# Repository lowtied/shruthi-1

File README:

Shruthi-1, a digital/analog hybrid MIDI monosynth.

This project is a redesign of the original Shruti-1, with a spec'ed up CPU,
and a focus on easy upgrades/modification of the analog section.
The ATMega644p allows new features in the firmware -- a larger selection of
oscillator algorithms, a bigger selection of wavetables, and a tiny sequencer.

Original developer: Emilie Gillet (emilie.o.gillet@gmail.com)

The firmware is released under a GPL3.0 license. It includes a
reimplementation of the formant synthesis algorithm used in Peter Knight's
Cantarino speech synthesizer.

The PCB layouts and schematics (in /hardware/shruthi/design/pcb)
are released under a Creative Commons cc-by-sa 3.0 license - except for some
discontinued filter boards which were released under a cc-by-nc-sa 3.0 license.

Documentation, analyses, simulations and 3D models are released under a
Creative Commons cc-by-sa 3.0 license.

PCB art:
- "saraswati" by Francois Barbut.
- "peacock_face" by Emilie Gillet.
- "radha" by Emilie Gillet.

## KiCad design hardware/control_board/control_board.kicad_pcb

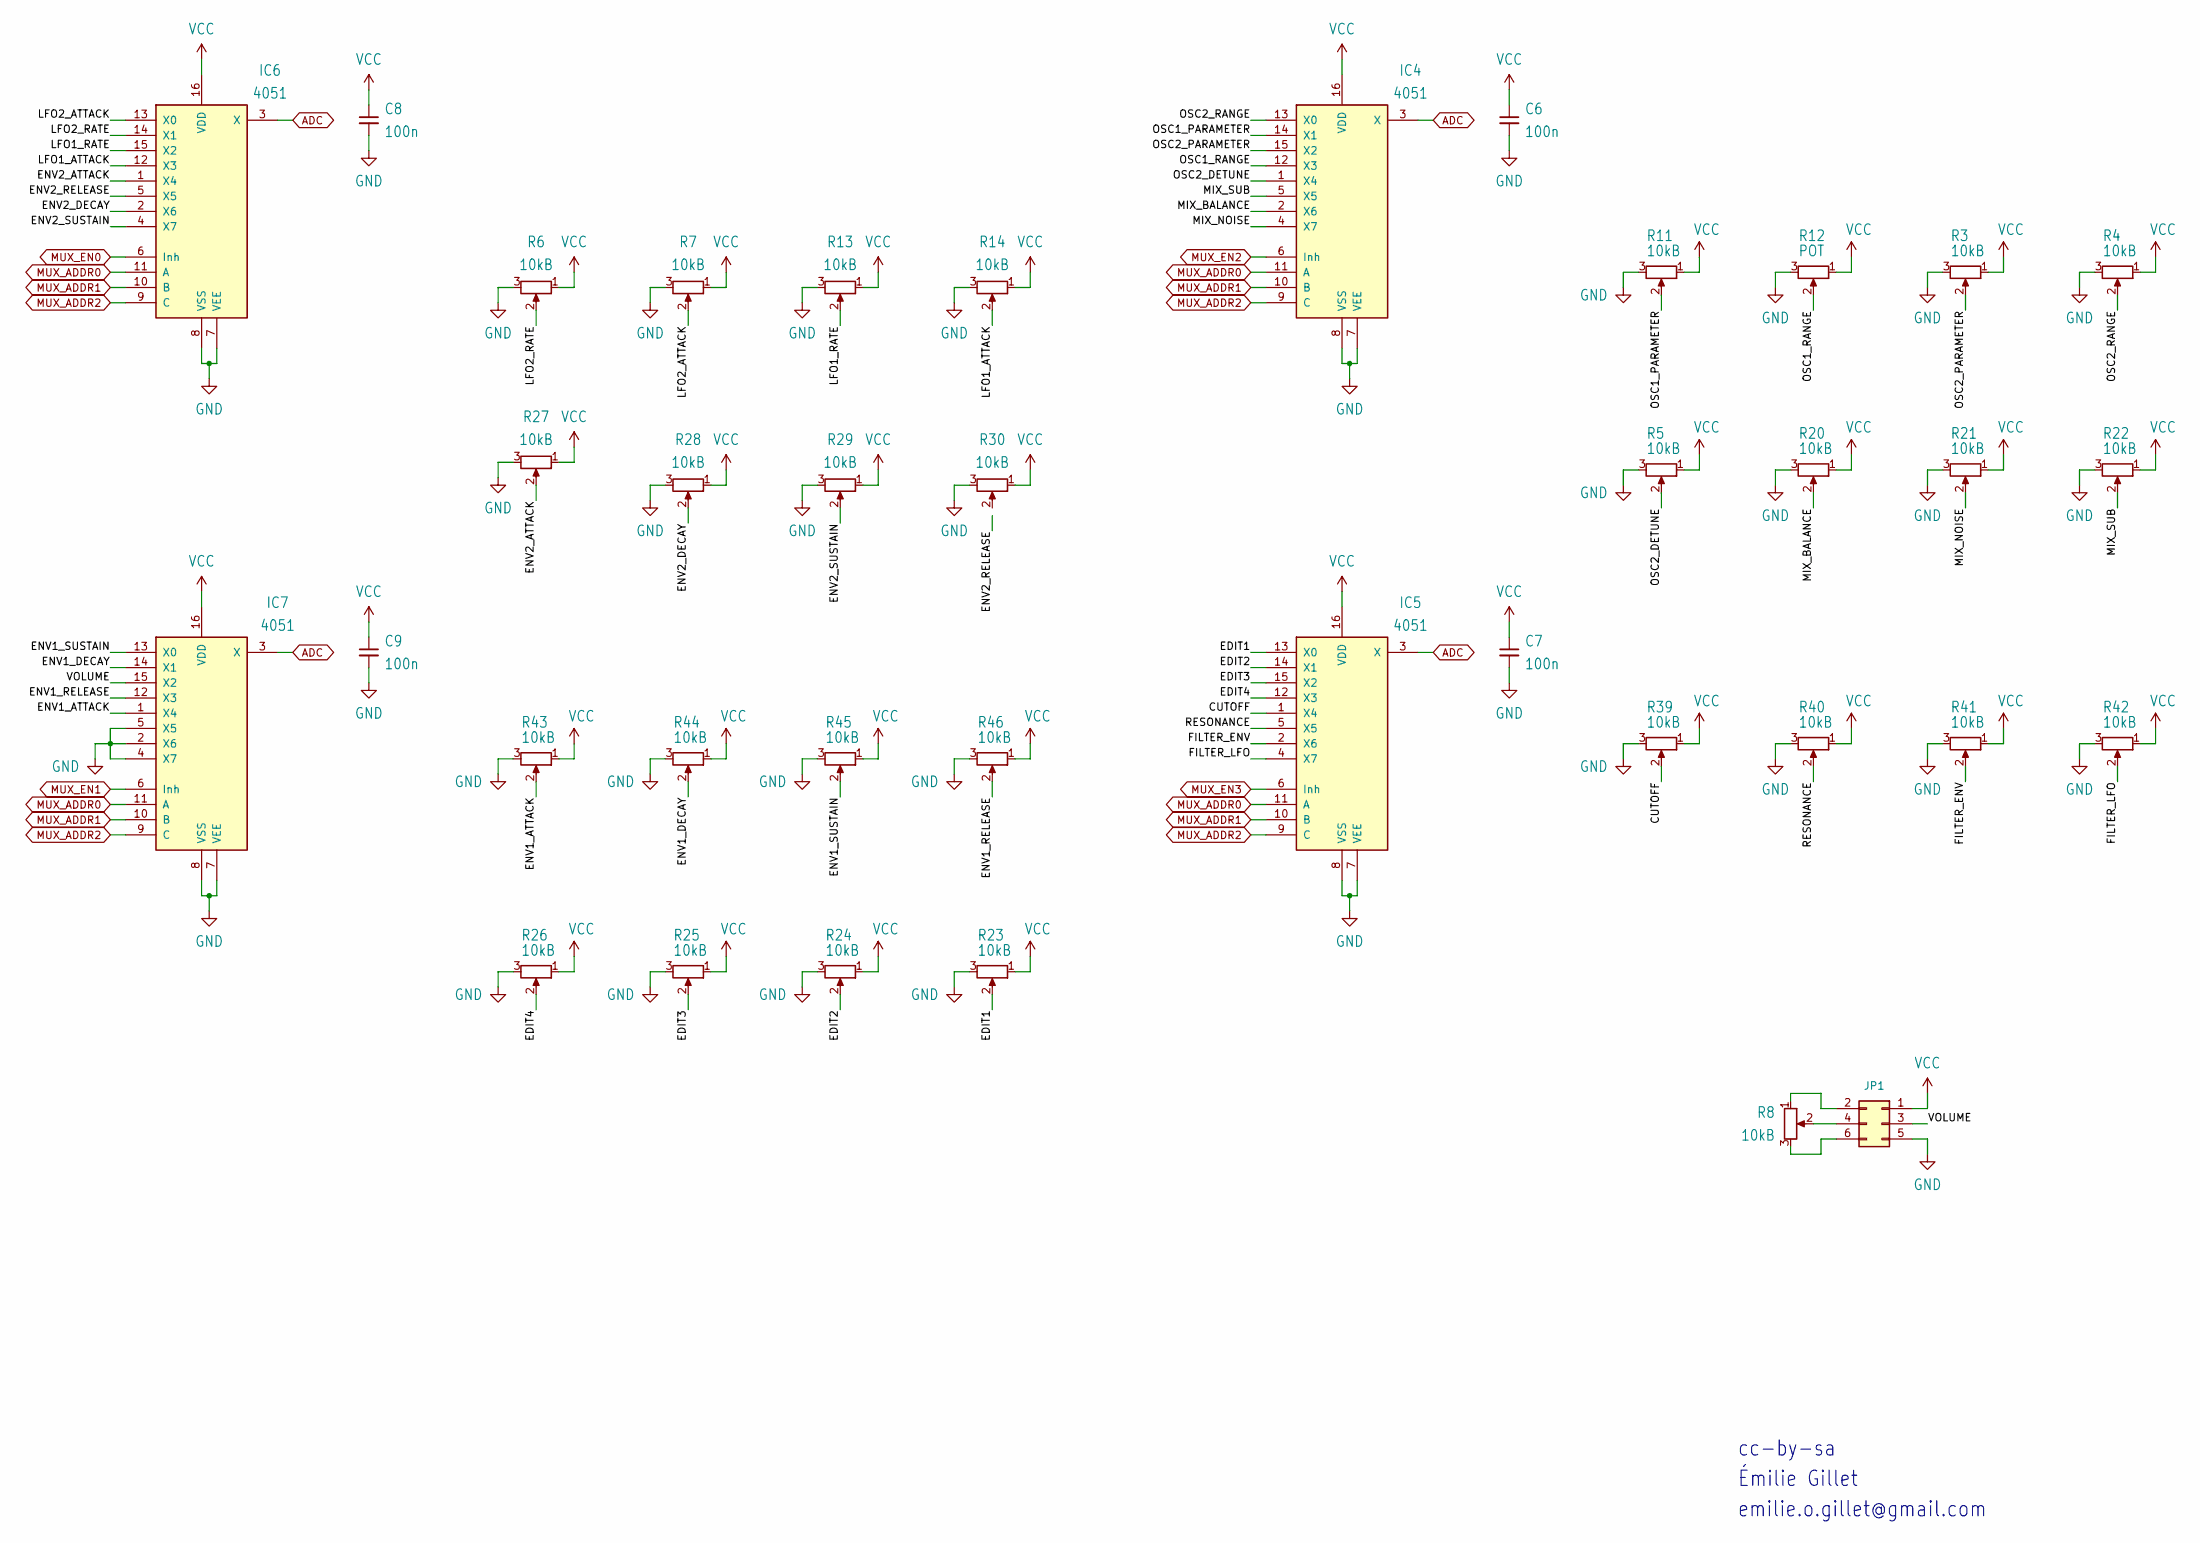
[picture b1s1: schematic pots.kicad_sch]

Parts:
C6, C7, C8, C9: 100n; C025-024X044
IC4, IC5, IC6, IC7: 4051; DIP-16_W7.62mm_Socket_LongPads
JP1: Conn_02x03_Odd_Even; PinHeader_2x03_P2.54mm_Vertical
R3, R4, R5, R6, R7, R8, R11, R13, R14, R20, R21, R22, R23, R24, R25, R26, R27, R28, R29, R30, R39, R40, R41, R42, R43, R44, R45, R46: 10kB; ALPS_POT_VERTICAL
R12: POT; ALPS_POT_VERTICAL

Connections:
/pots/CUTOFF: IC5.1 (X4), R39.2
/pots/EDIT1: IC5.13 (X0), R23.2
/pots/EDIT2: IC5.14 (X1), R24.2
/pots/EDIT3: IC5.15 (X2), R25.2
/pots/EDIT4: IC5.12 (X3), R26.2
/pots/ENV1_ATTACK: IC7.1 (X4), R43.2
/pots/ENV1_DECAY: IC7.14 (X1), R44.2
/pots/ENV1_RELEASE: IC7.12 (X3), R46.2
/pots/ENV1_SUSTAIN: IC7.13 (X0), R45.2
/pots/ENV2_ATTACK: IC6.1 (X4), R27.2
/pots/ENV2_DECAY: IC6.2 (X6), R28.2
/pots/ENV2_RELEASE: IC6.5 (X5)
/pots/ENV2_SUSTAIN: IC6.4 (X7), R29.2
/pots/FILTER_ENV: IC5.2 (X6), R41.2
/pots/FILTER_LFO: IC5.4 (X7), R42.2
/pots/LFO1_ATTACK: IC6.12 (X3), R14.2
/pots/LFO1_RATE: IC6.15 (X2), R13.2
/pots/LFO2_ATTACK: IC6.13 (X0), R7.2
/pots/LFO2_RATE: IC6.14 (X1), R6.2
/pots/MIX_BALANCE: IC4.2 (X6), R20.2
/pots/MIX_NOISE: IC4.4 (X7), R21.2
/pots/MIX_SUB: IC4.5 (X5), R22.2
/pots/OSC1_PARAMETER: IC4.14 (X1), R11.2
/pots/OSC1_RANGE: IC4.12 (X3), R12.2
/pots/OSC2_DETUNE: IC4.1 (X4), R5.2
/pots/OSC2_PARAMETER: IC4.15 (X2), R3.2
/pots/OSC2_RANGE: IC4.13 (X0), R4.2
/pots/RESONANCE: IC5.5 (X5), R40.2
/pots/VOLUME: IC7.15 (X2), JP1.3
ADC: IC4.3 (X), IC5.3 (X), IC6.3 (X), IC7.3 (X); also elsewhere on the board
GND: C6.2, C7.2, C8.2, C9.2, IC4.7 (VEE), IC4.8 (VSS), IC5.7 (VEE), IC5.8 (VSS), IC6.7 (VEE), IC6.8 (VSS), IC7.2 (X6), IC7.4 (X7), IC7.5 (X5), IC7.7 (VEE), IC7.8 (VSS), JP1.5, R3.3, R4.3, R5.3, R6.3, R7.3, R11.3, R12.3, R13.3, R14.3, R20.3, R21.3, R22.3, R23.3, R24.3, R25.3, R26.3, R27.3, R28.3, R29.3, R30.3, R39.3, R40.3, R41.3, R42.3, R43.3, R44.3, R45.3, R46.3; also elsewhere on the board
MUX_ADDR0: IC4.11 (A), IC5.11 (A), IC6.11 (A), IC7.11 (A); also elsewhere on the board
MUX_ADDR1: IC4.10 (B), IC5.10 (B), IC6.10 (B), IC7.10 (B); also elsewhere on the board
MUX_ADDR2: IC4.9 (C), IC5.9 (C), IC6.9 (C), IC7.9 (C); also elsewhere on the board
MUX_EN0: IC6.6 (Inh); also elsewhere on the board
MUX_EN1: IC7.6 (Inh); also elsewhere on the board
MUX_EN2: IC4.6 (Inh); also elsewhere on the board
MUX_EN3: IC5.6 (Inh); also elsewhere on the board
unnamed: JP1.2, R8.1
unnamed: JP1.4, R8.2
unnamed: JP1.6, R8.3
VCC: C6.1, C7.1, C8.1, C9.1, IC4.16 (VDD), IC5.16 (VDD), IC6.16 (VDD), IC7.16 (VDD), JP1.1, R3.1, R4.1, R5.1, R6.1, R7.1, R11.1, R12.1, R13.1, R14.1, R20.1, R21.1, R22.1, R23.1, R24.1, R25.1, R26.1, R27.1, R28.1, R29.1, R30.1, R39.1, R40.1, R41.1, R42.1, R43.1, R44.1, R45.1, R46.1; also elsewhere on the board

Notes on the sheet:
emilie.o.gillet@gmail.com
cc-by-sa
Émilie Gillet

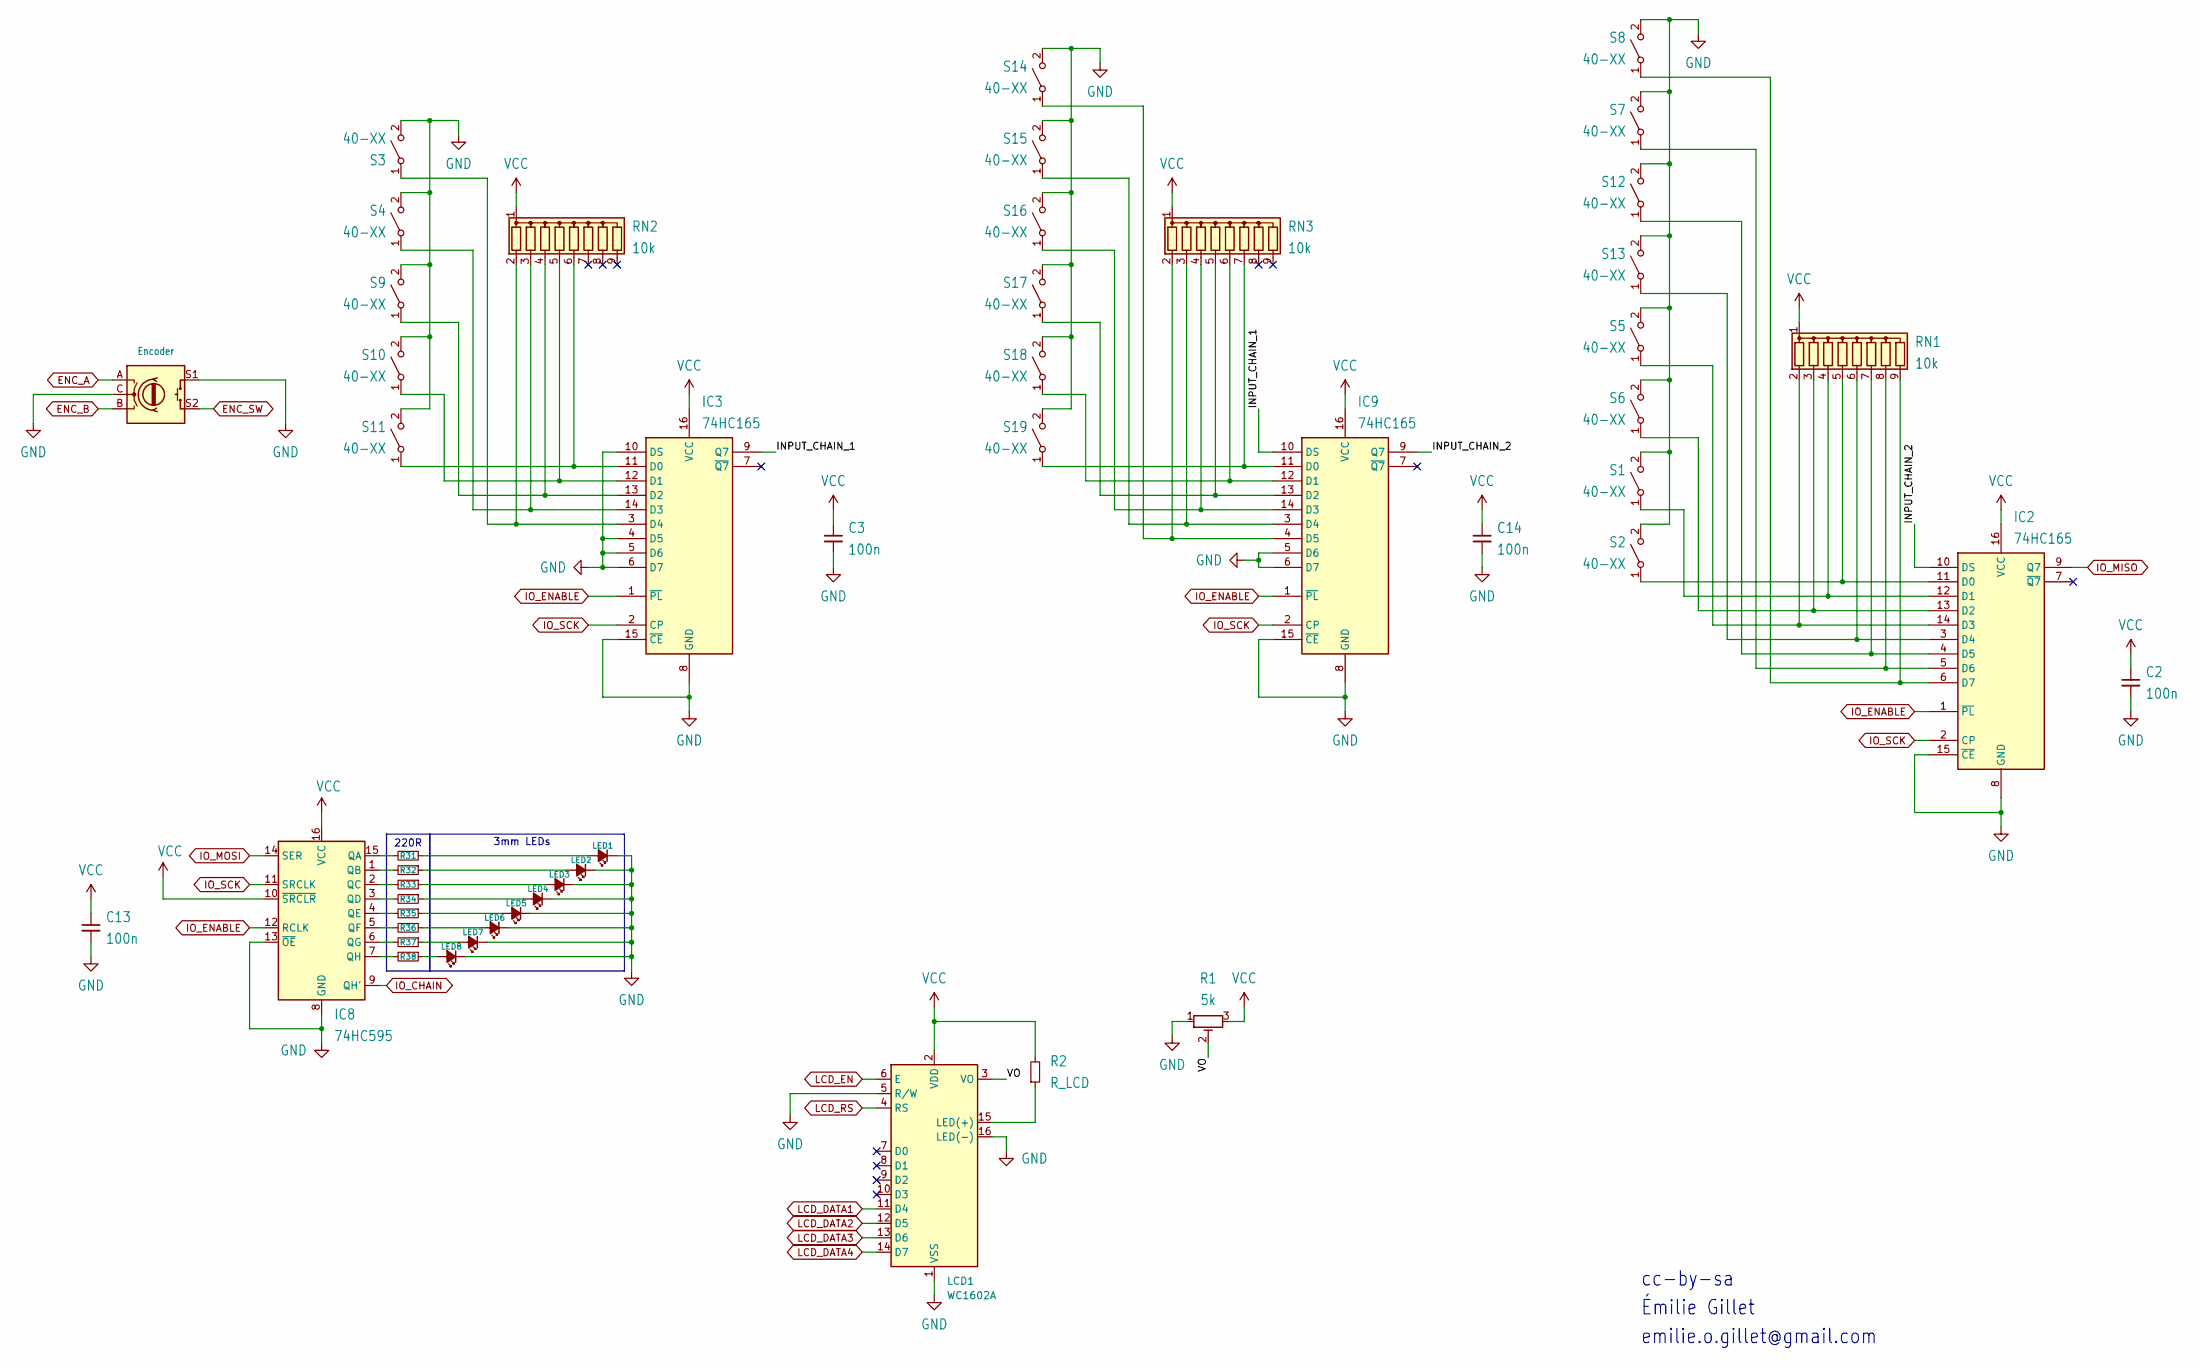
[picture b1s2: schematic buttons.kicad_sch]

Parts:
C2, C3, C13, C14: 100n; C025-024X044
IC2, IC3, IC9: 74HC165; DIP-16_W7.62mm_Socket_LongPads
IC8: 74HC595; DIP-16_W7.62mm_Socket_LongPads
LCD1: WC1602A
LED1, LED2, LED3, LED4, LED5, LED6, LED7, LED8: LED3MM; LED_D3.0mm
R1: 5k; Potentiometer_Bourns_3296W_Vertical
R2: R_LCD; R_Axial_DIN0204_L3.6mm_D1.6mm_P7.62mm_Horizontal
R31, R32, R33, R34, R35, R36, R37, R38: 220; R_Axial_DIN0204_L3.6mm_D1.6mm_P7.62mm_Horizontal
RN1, RN2, RN3: 10k; R_Array_SIP9
S1, S2, S3, S4, S5, S6, S7, S8, S9, S10, S11, S12, S13, S14, S15, S16, S17, S18, S19: 40-XX; B3F-40XX
SW1: Encoder; ALPS_EC12E_SW

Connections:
/buttons/INPUT_CHAIN_1: IC3.9 (Q7), IC9.10 (DS)
/buttons/INPUT_CHAIN_2: IC2.10 (DS), IC9.9 (Q7)
/buttons/VO: LCD1.3 (VO), R1.2
ENC_A: SW1.A; also elsewhere on the board
ENC_B: SW1.B; also elsewhere on the board
ENC_SW: SW1.S2; also elsewhere on the board
GND: C2.2, C3.2, C13.2, C14.2, IC2.8 (GND), IC2.15 (~CE), IC3.4 (D5), IC3.5 (D6), IC3.6 (D7), IC3.8 (GND), IC3.10 (DS), IC3.15 (~CE), IC8.8 (GND), IC8.13 (~OE), IC9.5 (D6), IC9.6 (D7), IC9.8 (GND), IC9.15 (~CE), LCD1.1 (VSS), LCD1.5 (R/W), LCD1.16 (LED(-)), LED1.1 (K), LED2.1 (K), LED3.1 (K), LED4.1 (K), LED5.1 (K), LED6.1 (K), LED7.1 (K), LED8.1 (K), R1.1, S1.2 (B), S2.2 (B), S3.2 (B), S4.2 (B), S5.2 (B), S6.2 (B), S7.2 (B), S8.2 (B), S9.2 (B), S10.2 (B), S11.2 (B), S12.2 (B), S13.2 (B), S14.2 (B), S15.2 (B), S16.2 (B), S17.2 (B), S18.2 (B), S19.2 (B), SW1.C, SW1.S1; also elsewhere on the board
IO_CHAIN: IC8.9 (QH'); also elsewhere on the board
IO_ENABLE: IC2.1 (~PL), IC3.1 (~PL), IC8.12 (RCLK), IC9.1 (~PL); also elsewhere on the board
IO_MISO: IC2.9 (Q7); also elsewhere on the board
IO_MOSI: IC8.14 (SER); also elsewhere on the board
IO_SCK: IC2.2 (CP), IC3.2 (CP), IC8.11 (SRCLK), IC9.2 (CP); also elsewhere on the board
LCD_DATA1: LCD1.11 (D4); also elsewhere on the board
LCD_DATA2: LCD1.12 (D5); also elsewhere on the board
LCD_DATA3: LCD1.13 (D6); also elsewhere on the board
LCD_DATA4: LCD1.14 (D7); also elsewhere on the board
LCD_EN: LCD1.6 (E); also elsewhere on the board
LCD_RS: LCD1.4 (RS); also elsewhere on the board
unnamed: IC2.11 (D0), RN1.5 (R4), S2.1 (A)
unnamed: IC2.12 (D1), RN1.4 (R3), S1.1 (A)
unnamed: IC2.13 (D2), RN1.3 (R2), S6.1 (A)
unnamed: IC2.14 (D3), RN1.2 (R1), S5.1 (A)
unnamed: IC2.3 (D4), RN1.6 (R5), S13.1 (A)
unnamed: IC2.4 (D5), RN1.7 (R6), S12.1 (A)
unnamed: IC2.5 (D6), RN1.8 (R7), S7.1 (A)
unnamed: IC2.6 (D7), RN1.9 (R8), S8.1 (A)
unnamed: IC3.11 (D0), RN2.6 (R5), S11.1 (A)
unnamed: IC3.12 (D1), RN2.5 (R4), S10.1 (A)
unnamed: IC3.13 (D2), RN2.4 (R3), S9.1 (A)
unnamed: IC3.14 (D3), RN2.3 (R2), S4.1 (A)
unnamed: IC3.3 (D4), RN2.2 (R1), S3.1 (A)
unnamed: IC8.15 (QA), R31.2
unnamed: IC8.1 (QB), R32.2
unnamed: IC8.2 (QC), R33.2
unnamed: IC8.3 (QD), R34.2
unnamed: IC8.4 (QE), R35.2
unnamed: IC8.5 (QF), R36.2
unnamed: IC8.6 (QG), R37.2
unnamed: IC8.7 (QH), R38.2
unnamed: IC9.11 (D0), RN3.7 (R6), S19.1 (A)
unnamed: IC9.12 (D1), RN3.6 (R5), S18.1 (A)
unnamed: IC9.13 (D2), RN3.5 (R4), S17.1 (A)
unnamed: IC9.14 (D3), RN3.4 (R3), S16.1 (A)
unnamed: IC9.3 (D4), RN3.3 (R2), S15.1 (A)
unnamed: IC9.4 (D5), RN3.2 (R1), S14.1 (A)
unnamed: LCD1.15 (LED(+)), R2.1
unnamed: LED1.2 (A), R31.1
unnamed: LED2.2 (A), R32.1
unnamed: LED3.2 (A), R33.1
unnamed: LED4.2 (A), R34.1
unnamed: LED5.2 (A), R35.1
unnamed: LED6.2 (A), R36.1
unnamed: LED7.2 (A), R37.1
unnamed: LED8.2 (A), R38.1
VCC: C2.1, C3.1, C13.1, C14.1, IC2.16 (VCC), IC3.16 (VCC), IC8.10 (~SRCLR), IC8.16 (VCC), IC9.16 (VCC), LCD1.2 (VDD), R1.3, R2.2, RN1.1 (common), RN2.1 (common), RN3.1 (common); also elsewhere on the board

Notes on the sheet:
220R
3mm LEDs
emilie.o.gillet@gmail.com
Émilie Gillet
cc-by-sa

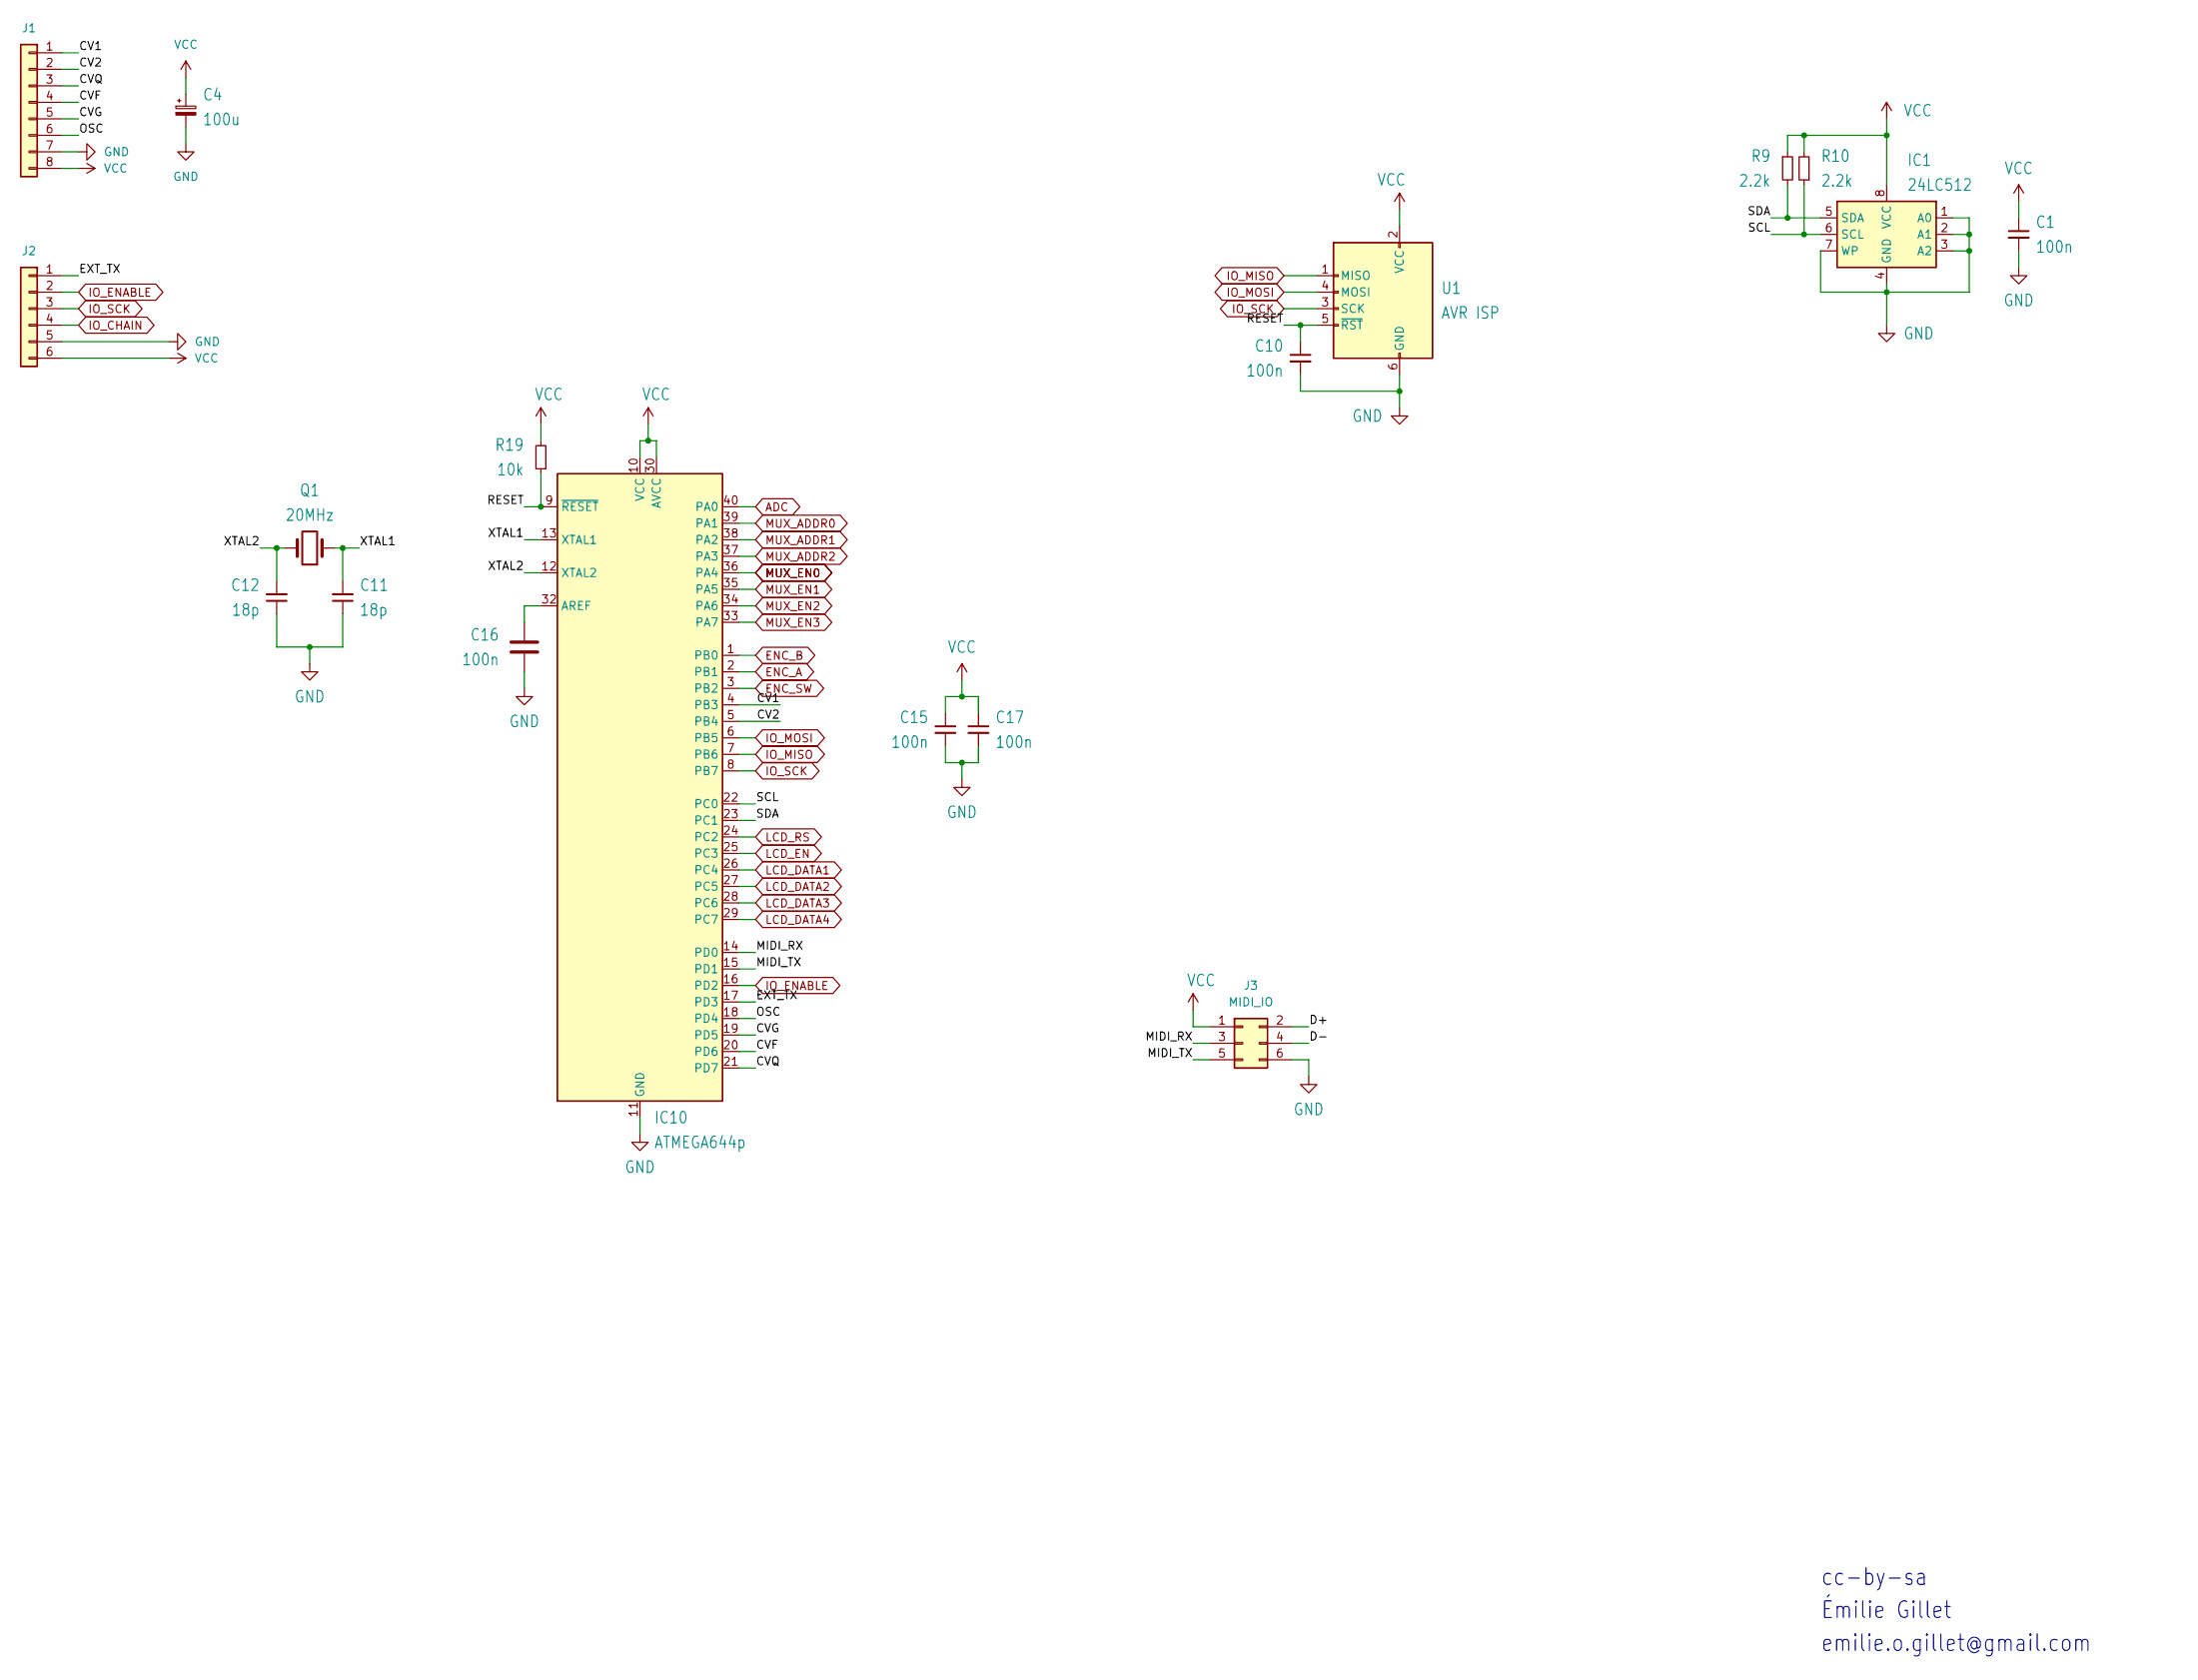
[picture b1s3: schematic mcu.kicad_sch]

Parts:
C1, C10, C15, C16, C17: 100n; C025-024X044
C4: 100u; CP_Radial_D6.3mm_P2.50mm
C11, C12: 18p; C025-024X044
IC1: 24LC512; DIP-8_W7.62mm_Socket_LongPads
IC10: ATMEGA644p; DIP-40_W15.24mm_Socket_LongPads
J1: Conn_01x08; PinHeader_1x08_P2.54mm_Vertical
J2: Conn_01x06; PinHeader_1x06_P2.54mm_Vertical
J3: MIDI_IO; PinHeader_2x03_P2.54mm_Vertical
Q1: 20MHz; HC49U-V
R9, R10: 2.2k; R_Axial_DIN0204_L3.6mm_D1.6mm_P7.62mm_Horizontal
R19: 10k; 0204_7
U1: AVR ISP; PinHeader_2x03_P2.54mm_Vertical

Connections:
/mcu/CV1: IC10.4 (PB3), J1.1
/mcu/CV2: IC10.5 (PB4), J1.2
/mcu/CVF: IC10.20 (PD6), J1.4
/mcu/CVG: IC10.19 (PD5), J1.5
/mcu/CVQ: IC10.21 (PD7), J1.3
/mcu/D+: J3.2
/mcu/D-: J3.4
/mcu/EXT_TX: IC10.17 (PD3), J2.1
/mcu/MIDI_RX: IC10.14 (PD0), J3.3
/mcu/MIDI_TX: IC10.15 (PD1), J3.5
/mcu/OSC: IC10.18 (PD4), J1.6
/mcu/RESET: C10.1, IC10.9 (~RESET), R19.1, U1.5 (~RST)
/mcu/SCL: IC1.6 (SCL), IC10.22 (PC0), R10.1
/mcu/SDA: IC1.5 (SDA), IC10.23 (PC1), R9.2
/mcu/XTAL1: C11.2, IC10.13 (XTAL1), Q1.1
/mcu/XTAL2: C12.2, IC10.12 (XTAL2), Q1.2
ADC: IC10.40 (PA0); also elsewhere on the board
ENC_A: IC10.2 (PB1); also elsewhere on the board
ENC_B: IC10.1 (PB0); also elsewhere on the board
ENC_SW: IC10.3 (PB2); also elsewhere on the board
GND: C1.2, C4.2, C10.2, C11.1, C12.1, C15.2, C16.2, C17.2, IC1.1 (A0), IC1.2 (A1), IC1.3 (A2), IC1.4 (GND), IC1.7 (WP), IC10.11 (GND), IC10.31 (GND), J1.7, J2.5, J3.6, U1.6 (GND); also elsewhere on the board
IO_CHAIN: J2.4; also elsewhere on the board
IO_ENABLE: IC10.16 (PD2), J2.2; also elsewhere on the board
IO_MISO: IC10.7 (PB6), U1.1 (MISO); also elsewhere on the board
IO_MOSI: IC10.6 (PB5), U1.4 (MOSI); also elsewhere on the board
IO_SCK: IC10.8 (PB7), J2.3, U1.3 (SCK); also elsewhere on the board
LCD_DATA1: IC10.26 (PC4); also elsewhere on the board
LCD_DATA2: IC10.27 (PC5); also elsewhere on the board
LCD_DATA3: IC10.28 (PC6); also elsewhere on the board
LCD_DATA4: IC10.29 (PC7); also elsewhere on the board
LCD_EN: IC10.25 (PC3); also elsewhere on the board
LCD_RS: IC10.24 (PC2); also elsewhere on the board
MUX_ADDR0: IC10.39 (PA1); also elsewhere on the board
MUX_ADDR1: IC10.38 (PA2); also elsewhere on the board
MUX_ADDR2: IC10.37 (PA3); also elsewhere on the board
MUX_EN0: IC10.36 (PA4); also elsewhere on the board
MUX_EN1: IC10.35 (PA5); also elsewhere on the board
MUX_EN2: IC10.34 (PA6); also elsewhere on the board
MUX_EN3: IC10.33 (PA7); also elsewhere on the board
unnamed: C16.1, IC10.32 (AREF)
VCC: C1.1, C4.1, C15.1, C17.1, IC1.8 (VCC), IC10.10 (VCC), IC10.30 (AVCC), J1.8, J2.6, J3.1, R9.1, R10.2, R19.2, U1.2 (VCC); also elsewhere on the board

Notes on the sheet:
cc-by-sa
Émilie Gillet
emilie.o.gillet@gmail.com

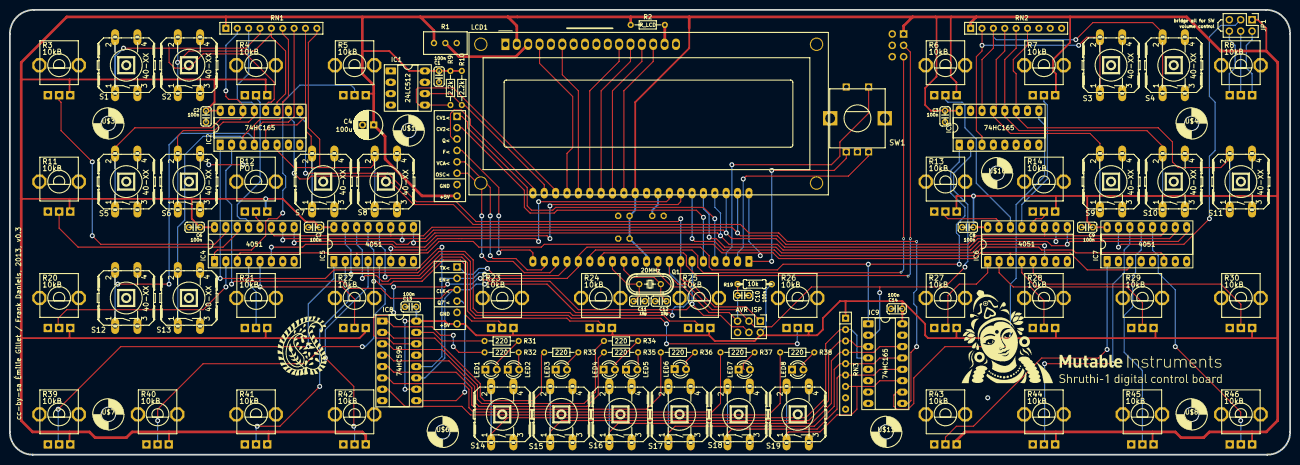
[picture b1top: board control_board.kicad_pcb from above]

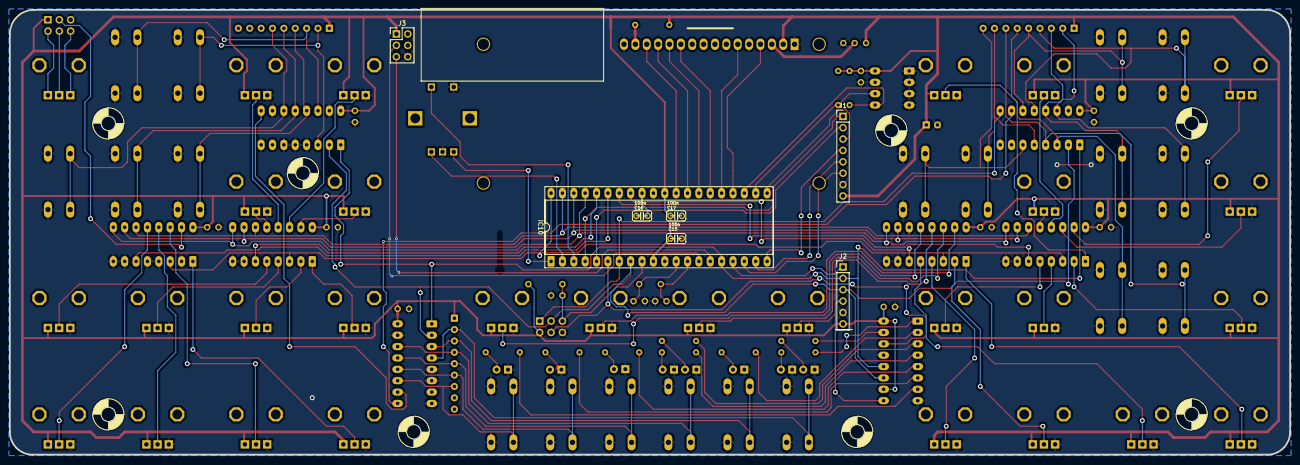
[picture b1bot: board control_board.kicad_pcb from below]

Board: 2 copper layers, 286.0 x 99.4 mm, 116 parts (7 on the bottom side), 109 nets.

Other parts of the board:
U$1, U$3, U$4, U$6, U$7, U$8, U$10, U$11: MountingHole_M3
U$5: V2_LOGO_SHRUTHI_DIGITAL
U$9: V2_LOGO_DINGBAT1

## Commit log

2025-06-11 update git submodules
2025-06-11 move graphics into resources directory and move art credits to main readme
2025-06-11 move graphic from dsp board into resources folder
2025-06-11 move boards into seperate folders, remove uneeded boards
2025-06-11 move enclosure design files to enclosure directory
2025-06-11 move documentation files into docs folder
2025-06-11 move source files and folders to firmware folder
2025-06-11 remove v02 svf filter board due to errors in eagle project
2025-06-11 update all eagle projects to latest versions
2025-06-11 update gitignore
2025-06-11 import eagle project into kicad
2025-06-17 center q1 between r24 and r25, increase spacing between c11 and c12
2025-06-17 add mounting hole footprint
2025-06-17 use new mounting hole footprint
2025-06-17 remove extra worksheet frame
2025-06-17 update capacitors to use kicad symbols
2025-06-17 update jumpers to use kicad symbols
2025-06-19 update crystal to use kicad symbols
2025-06-19 update vcc to use kicad symbols
2025-06-19 update gnd to use kicad symbols
2025-06-19 update resistors to use kicad symbols
2025-06-19 update atmega644p to use kicad symbols
2025-06-20 add atmega644p datasheet
2025-06-20 use relative path for footprints library
2025-06-20 move libraries directory to root of repository
2025-06-20 move enclosure files to cad directory
2025-06-20 update 24LC512 to use kicad symbols
2025-06-20 remove sidekick board
2025-06-20 update AVR ISP to use kicad symbols
2025-06-20 update MIDI circuitry to use kicad symbols
2025-06-20 move bypass capacitors next to respective devices
2025-06-23 fix footprint library location
2025-06-23 update footprints for atmega and 6N137
2025-06-23 add datasheet for 4051
2025-06-23 update 4051 to use kicad symbols
2025-06-23 update 4051 footprints
2025-06-23 update pots to use kicad symbols
2025-06-23 remove aligment lines from User.4 layer
2025-06-23 fix pin numbering for pot footprint
2025-06-23 update volume jumpers to use kicad symbols
2025-06-23 update 75HC165s to use kicad symbols
2025-06-23 update resistor networks to use kicad symbols
2025-06-23 add SN74HC165 datasheet
2025-06-23 fix extra connections on IC2
2025-06-23 update switches to use kicad symbols
2025-06-23 update footprints on pcb and fix a few minor errors
2025-06-23 remove top fill zone and replace bottom fill zone
2025-06-23 update 74HC165 footprints
2025-06-23 update 74HC595 and LED symbols
2025-06-23 remove loose wires and text
2025-06-23 update LCD parts to use kicad symbols
2025-06-23 use original LCD footprint for now
2025-06-24 use 1x8 header instead of separate ones for J1 and J2
2025-06-24 update position of board to board connectors
2025-06-24 update LED and LED resistor footprints
2025-06-24 update footprint for 74HC595
2025-06-24 update silkscreen for 74HC165s
2025-06-24 update silkscreen for 4051s
2025-06-24 update footprint and silkscreen for volume jumpers
2025-06-24 update footprint and silkscreen for isp header
2025-06-24 update footprints and silkscreen for optocoupler circuitry
2025-06-24 add 24LC512 datasheet
2025-06-24 update footprints and silkscreen for 24LC512 circuitry
2025-06-24 update footprints and silkscreen for big cap
2025-06-24 ignore file that tracks autosave files
2025-06-24 remove imported eagle symbols
2025-06-30 remove files related to everything except shruthi-xt
2025-06-30 consolidate files related to shruthi-xt into flatter structure
2025-06-30 rename control board kicad project
2025-06-30 rename sheets
2025-06-30 update symbol and footprint for display
2025-06-30 update lcd LED and trimmer footprints
2025-06-30 move midi components to daughterboard
2025-07-01 move all logic components to daughterboard, move MIDI to new board

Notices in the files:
hardware/control_board/control_board.kicad_pcb:
cc-by-sa Émilie Gillet / Frank Daniels, 2013, v0.3
